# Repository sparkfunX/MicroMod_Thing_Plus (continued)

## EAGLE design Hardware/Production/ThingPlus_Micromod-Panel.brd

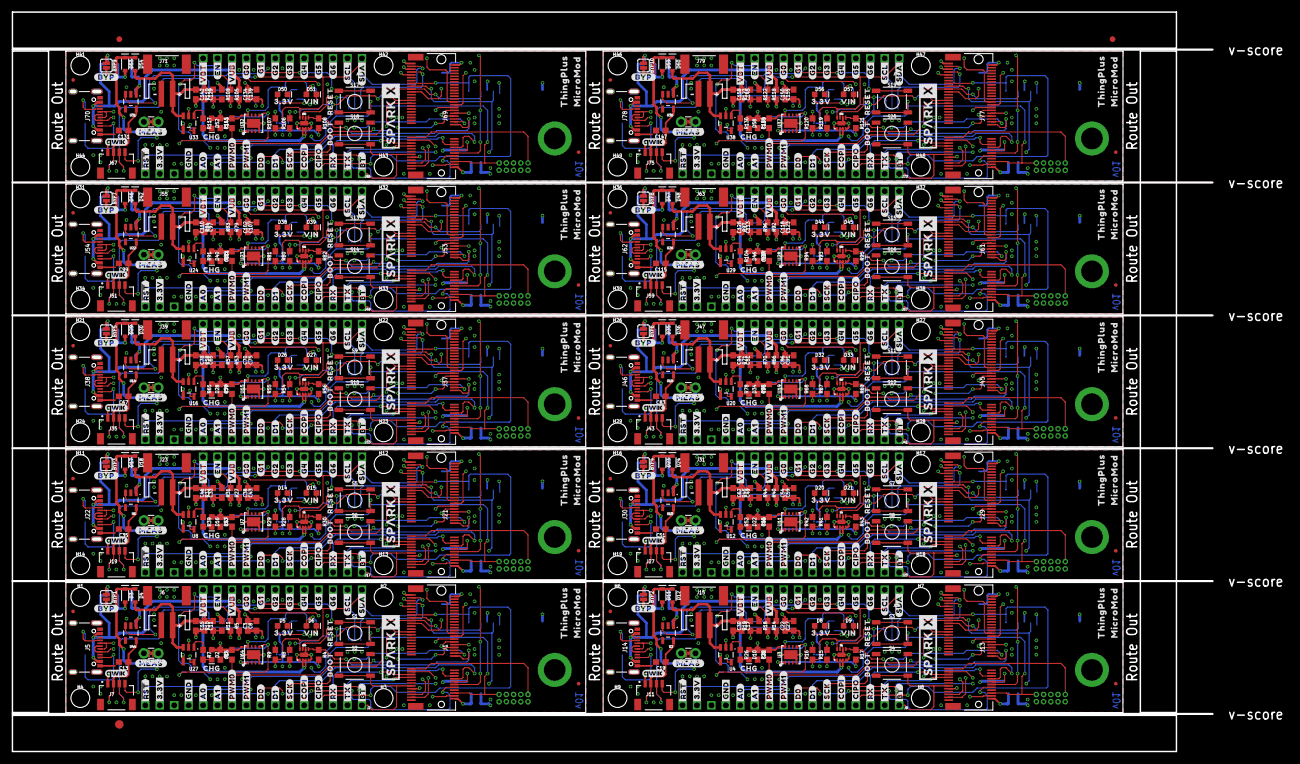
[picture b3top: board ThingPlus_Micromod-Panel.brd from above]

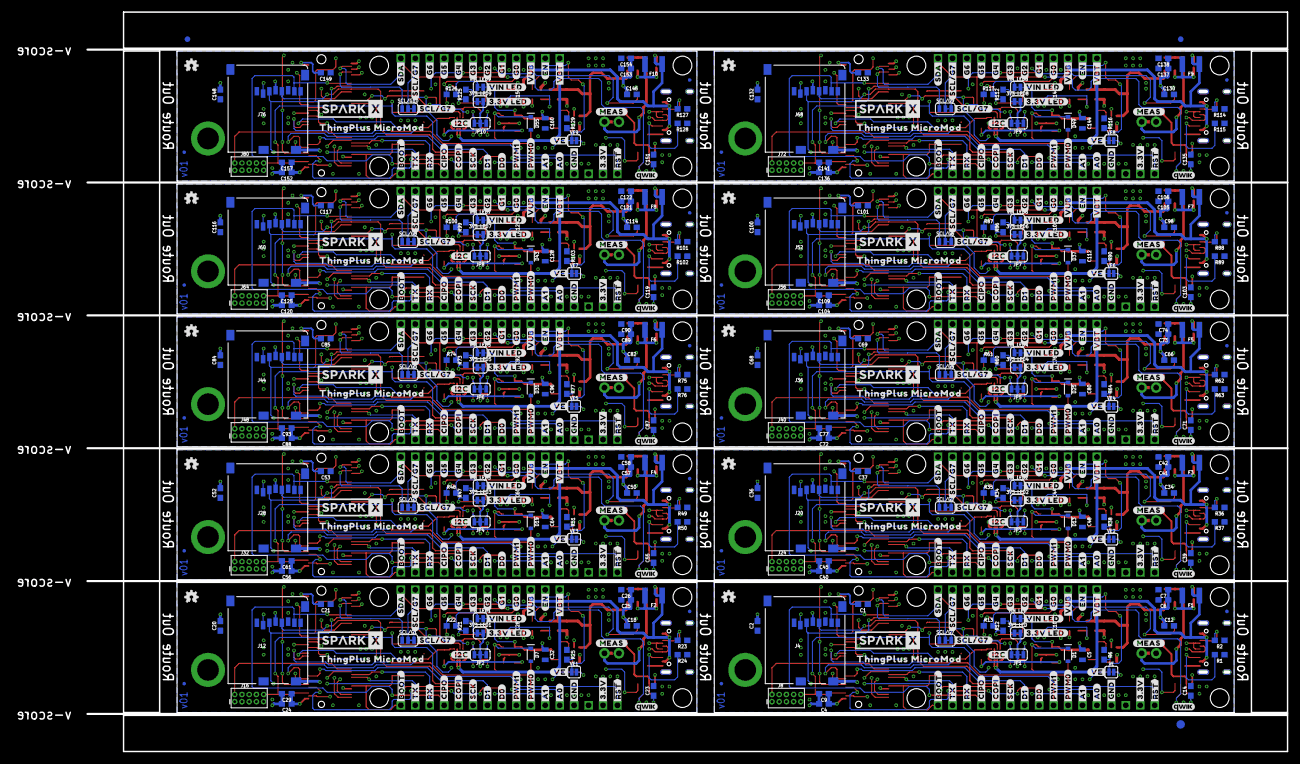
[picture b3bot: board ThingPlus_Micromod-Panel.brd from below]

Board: 4 copper layers, 211.1 x 130.0 mm, 1446 parts (623 on the bottom side), 530 nets.

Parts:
3V3_LED, 3V3_LED1, 3V3_LED2, 3V3_LED3, 3V3_LED4, 3V3_LED5, 3V3_LED6, 3V3_LED7, 3V3_LED8, 3V3_LED9: SMT-JUMPER_2_NC_TRACE_SILK
BYP1, BYP2, BYP3, BYP4, BYP5, BYP6, BYP7, BYP8, BYP9, BYP10: JUMPER-SMT_2_NO_SILK; SMT-JUMPER_2_NO_SILK
C1, C3, C4, C7, C10, C11, C14, C17, C21, C22, C23, C24, C26, C28, C33, C37, C38, C39, C40, C42, C44, C49, C53, C54, C55, C56, C58, C60, C65, C69, C70, C71, C72, C74, C76, C81, C85, C86, C87, C88, C90, C92, C97, C101, C102, C103, C104, C106, C108, C113, C117, C118, C119, C120, C122, C124, C129, C133, C134, C135, C136, C138, C140, C145, C149, C150, C151, C152, C154, C156: 0.1uF; 0603
C2, C8, C12, C13, C18, C19, C20, C27, C34, C35, C36, C43, C50, C51, C52, C59, C66, C67, C68, C75, C82, C83, C84, C91, C98, C99, C100, C107, C114, C115, C116, C123, C130, C131, C132, C139, C146, C147, C148, C155: 1.0uF; 0603
C5, C32, C48, C64, C80, C96, C112, C128, C144, C160: 10uF; 0805
C6, C9, C25, C29, C41, C45, C57, C61, C73, C77, C89, C93, C105, C109, C121, C125, C137, C141, C153, C157: 0.22uF; 0603
C15, C16, C30, C31, C46, C47, C62, C63, C78, C79, C94, C95, C110, C111, C126, C127, C142, C143, C158, C159: 4.7uF; 0603
CURR_MEAS, CURR_MEAS1, CURR_MEAS2, CURR_MEAS3, CURR_MEAS4, CURR_MEAS5, CURR_MEAS6, CURR_MEAS7, CURR_MEAS8, CURR_MEAS9: COMBO-JUMPER_2_NC_TRACE
D1, D7, D13, D19, D25, D31, D37, D43, D49, D55: 3.3V; SOD-323
D2, D6, D9, D10, D15, D16, D21, D22, D27, D28, D33, D34, D39, D40, D45, D46, D51, D52, D57, D58: Yellow; LED-0603
D3, D4, D11, D12, D17, D18, D23, D24, D29, D30, D35, D36, D41, D42, D47, D48, D53, D54, D59, D60: 3A/10V/280mV; SOD-323
D5, D8, D14, D20, D26, D32, D38, D44, D50, D56: RED; LED-0603
E$1, E$2, E$3, E$4: FIDUCIAL-1X2
E$5, E$6: FIDUCIAL-1.5X3
F1, F2, F3, F4, F5, F6, F7, F8, F9, F10: 6V/2A; 1210
FD1, FD2, FD3, FD4, FD5, FD6, FD7, FD8, FD9, FD10, FD11, FD12, FD13, FD14, FD15, FD16, FD17, FD18, FD19, FD20, FD21, FD22, FD23, FD24, FD25, FD26, FD27, FD28, FD29, FD30, FD31, FD32, FD33, FD34, FD35, FD36, FD37, FD38, FD39, FD40: FIDUCIALUFIDUCIAL; FIDUCIAL-MICRO
FRAME1, FRAME2, FRAME3, FRAME4, FRAME5, FRAME6, FRAME7, FRAME8, FRAME9, FRAME10: FRAME-LEDGER; CREATIVE_COMMONS
H1, H2, H3, H4, H6, H7, H8, H9, H11, H12, H13, H14, H16, H17, H18, H19, H21, H22, H23, H24, H26, H27, H28, H29, H31, H32, H33, H34, H36, H37, H38, H39, H41, H42, H43, H44, H46, H47, H48, H49: STAND-OFF
H5, H10, H15, H20, H25, H30, H35, H40, H45, H50: STAND-OFF-REFLOW2.5MM_TALL; STAND-OFF-REFLOW-M2.5
J1, J13, J21, J29, J37, J45, J53, J61, J69, J77: MICROMOD-2222-C; M.2-CONNECTOR-E
J2, J9, J17, J25, J33, J41, J49, J57, J65, J73: 1X16_SM_SQ_NOSILK
J3, J10, J18, J26, J34, J42, J50, J58, J66, J74: 1X12_SM_SQ_NOSILK
J4, J12, J20, J28, J36, J44, J52, J60, J68, J76: MICRO-SD-SDIOPUSH-PUSH; MICRO-SD-SOCKET
J5, J14, J22, J30, J38, J46, J54, J62, J70, J78: USB-C-16P_4LAYER-PADS
J6, J15, J23, J31, J39, J47, J55, J63, J71, J79: JST-2-SMD
J7, J11, J19, J27, J35, J43, J51, J59, J67, J75: QWIIC_RIGHT_ANGLE; JST04_1MM_RA
J8, J16, J24, J32, J40, J48, J56, J64, J72, J80: JTAG; 2X5-PTH-1.27MM
JP1, JP2, JP3, JP4, JP5, JP6, JP7, JP8, JP9, JP10: JUMPER-SMT_3_2-NC_TRACE_SILK; SMT-JUMPER_3_2-NC_TRACE_SILK
LOGO1, LOGO4, LOGO7, LOGO10, LOGO13, LOGO16, LOGO19, LOGO22, LOGO25, LOGO28: OSHW-LOGOMINI; OSHW-LOGO-MINI
LOGO2, LOGO3, LOGO5, LOGO6, LOGO8, LOGO9, LOGO11, LOGO12, LOGO14, LOGO15, LOGO17, LOGO18, LOGO20, LOGO21, LOGO23, LOGO24, LOGO26, LOGO27, LOGO29, LOGO30: QWIIC_LOGO_4MM; QWIIC_4MM
R1, R2, R23, R24, R36, R37, R49, R50, R62, R63, R75, R76, R88, R89, R101, R102, R114, R115, R127, R128: 5.1k; 0603
R3, R5, R14, R20, R27, R33, R40, R46, R53, R59, R66, R72, R79, R85, R92, R98, R105, R111, R118, R124: 100k; 0603
R4, R11, R17, R18, R30, R31, R43, R44, R56, R57, R69, R70, R82, R83, R95, R96, R108, R109, R121, R122: 10k; 0603
R6, R8, R9, R15, R16, R25, R28, R29, R38, R41, R42, R51, R54, R55, R64, R67, R68, R77, R80, R81, R90, R93, R94, R103, R106, R107, R116, R119, R120, R129: 2.2k; 0603
R7, R12, R21, R26, R34, R39, R47, R52, R60, R65, R73, R78, R86, R91, R99, R104, R112, R117, R125, R130: 1k; 0603
R10, R19, R32, R45, R58, R71, R84, R97, R110, R123: 20k; 0603
R13, R22, R35, R48, R61, R74, R87, R100, R113, R126: 4.7k; 0603
S1, S3, S5, S7, S9, S11, S13, S15, S17, S19: Reset; TACTILE_SWITCH_SMD_5.2MM
S2, S4, S6, S8, S10, S12, S14, S16, S18, S20: BOOT; TACTILE_SWITCH_SMD_5.2MM
SCL/G1, SCL/G2, SCL/G3, SCL/G4, SCL/G5, SCL/G6, SCL/G7, SCL/G8, SCL/G9, SCL/G10: JUMPER-SMT_3_1-NC_TRACE_SILK; SMT-JUMPER_3_1-NC_TRACE_SILK
U1, U5, U9, U13, U17, U21, U25, U30, U34, U35: MAX17048; DFN-8
U2, U6, U10, U14, U18, U22, U26, U31, U36, U44: 3.3V; SOT23-5
U3, U7, U11, U15, U19, U23, U28, U32, U37, U64: AP7361C-33; UDFN-8
U4, U8, U12, U16, U20, U24, U27, U29, U33, U38: MCP73831; SOT23-5
U$1, U$2, U$75, U$76, U$149, U$150, U$223, U$224, U$297, U$298, U$371, U$372, U$445, U$446, U$519, U$520, U$593, U$594, U$667, U$668: SPARKX-LOGO5; SPARKX-LARGE
U$3, U$77, U$151, U$225, U$299, U$373, U$447, U$521, U$595, U$669: ##BT##11
U$4, U$42, U$78, U$114, U$152, U$188, U$226, U$262, U$300, U$336, U$374, U$410, U$448, U$484, U$522, U$558, U$596, U$632, U$670, U$706: #TX#9
U$5, U$43, U$79, U$115, U$153, U$189, U$227, U$263, U$301, U$337, U$375, U$411, U$449, U$485, U$523, U$559, U$597, U$633, U$671, U$707: #RX#8
U$6, U$44, U$80, U$116, U$154, U$190, U$228, U$264, U$302, U$338, U$376, U$412, U$450, U$486, U$524, U$560, U$598, U$634, U$672, U$708: #CIPO#7
U$7, U$45, U$81, U$117, U$155, U$191, U$229, U$265, U$303, U$339, U$377, U$413, U$451, U$487, U$525, U$561, U$599, U$635, U$673, U$709: #COPI#6
U$8, U$46, U$82, U$118, U$156, U$192, U$230, U$266, U$304, U$340, U$378, U$414, U$452, U$488, U$526, U$562, U$600, U$636, U$674, U$710: #SCK#5
U$9, U$47, U$83, U$119, U$157, U$193, U$231, U$267, U$305, U$341, U$379, U$415, U$453, U$489, U$527, U$563, U$601, U$637, U$675, U$711: #D1#5
U$10, U$48, U$84, U$120, U$158, U$194, U$232, U$268, U$306, U$342, U$380, U$416, U$454, U$490, U$528, U$564, U$602, U$638, U$676, U$712: #D0#5
U$11, U$49, U$85, U$121, U$159, U$195, U$233, U$269, U$307, U$343, U$381, U$417, U$455, U$491, U$529, U$565, U$603, U$639, U$677, U$713: #PWM0#5
U$12, U$50, U$86, U$122, U$160, U$196, U$234, U$270, U$308, U$344, U$382, U$418, U$456, U$492, U$530, U$566, U$604, U$640, U$678, U$714: #PWM1#5
U$13, U$51, U$87, U$123, U$161, U$197, U$235, U$271, U$309, U$345, U$383, U$419, U$457, U$493, U$531, U$567, U$605, U$641, U$679, U$715: #A1#5
U$14, U$52, U$88, U$124, U$162, U$198, U$236, U$272, U$310, U$346, U$384, U$420, U$458, U$494, U$532, U$568, U$606, U$642, U$680, U$716: #A0#5
U$15, U$53, U$89, U$125, U$163, U$199, U$237, U$273, U$311, U$347, U$385, U$421, U$459, U$495, U$533, U$569, U$607, U$643, U$681, U$717: #GND#4
U$16, U$54, U$90, U$126, U$164, U$200, U$238, U$274, U$312, U$348, U$386, U$422, U$460, U$496, U$534, U$570, U$608, U$644, U$682, U$718: #3#3V#1
U$17, U$55, U$91, U$127, U$165, U$201, U$239, U$275, U$313, U$349, U$387, U$423, U$461, U$497, U$535, U$571, U$609, U$645, U$683, U$719: ##RST##0
U$18, U$66, U$92, U$140, U$166, U$214, U$240, U$288, U$314, U$362, U$388, U$436, U$462, U$510, U$536, U$584, U$610, U$658, U$684, U$732: #MEAS#25
U$19, U$93, U$167, U$241, U$315, U$389, U$463, U$537, U$611, U$685: CHG20
U$20, U$94, U$168, U$242, U$316, U$390, U$464, U$538, U$612, U$686: RESET19
U$21, U$95, U$169, U$243, U$317, U$391, U$465, U$539, U$613, U$687: BOOT18
U$22, U$57, U$96, U$129, U$170, U$203, U$244, U$277, U$318, U$351, U$392, U$425, U$466, U$499, U$540, U$573, U$614, U$647, U$688, U$721: #VBT#16
U$23, U$58, U$97, U$130, U$171, U$204, U$245, U$278, U$319, U$352, U$393, U$426, U$467, U$500, U$541, U$574, U$615, U$648, U$689, U$722: #EN#15
U$24, U$59, U$98, U$131, U$172, U$205, U$246, U$279, U$320, U$353, U$394, U$427, U$468, U$501, U$542, U$575, U$616, U$649, U$690, U$723: #G0#14
U$25, U$60, U$99, U$132, U$173, U$206, U$247, U$280, U$321, U$354, U$395, U$428, U$469, U$502, U$543, U$576, U$617, U$650, U$691, U$724: #G1#14
U$26, U$61, U$100, U$133, U$174, U$207, U$248, U$281, U$322, U$355, U$396, U$429, U$470, U$503, U$544, U$577, U$618, U$651, U$692, U$725: #G2#14
U$27, U$62, U$101, U$134, U$175, U$208, U$249, U$282, U$323, U$356, U$397, U$430, U$471, U$504, U$545, U$578, U$619, U$652, U$693, U$726: #G3#14
U$28, U$63, U$102, U$135, U$176, U$209, U$250, U$283, U$324, U$357, U$398, U$431, U$472, U$505, U$546, U$579, U$620, U$653, U$694, U$727: #G4#14
U$29, U$64, U$103, U$136, U$177, U$210, U$251, U$284, U$325, U$358, U$399, U$432, U$473, U$506, U$547, U$580, U$621, U$654, U$695, U$728: #G5#14
U$30, U$65, U$104, U$137, U$178, U$211, U$252, U$285, U$326, U$359, U$400, U$433, U$474, U$507, U$548, U$581, U$622, U$655, U$696, U$729: #G6#14
U$31, U$105, U$179, U$253, U$327, U$401, U$475, U$549, U$623, U$697: #SCL#13
U$32, U$67, U$106, U$138, U$180, U$212, U$254, U$286, U$328, U$360, U$402, U$434, U$476, U$508, U$550, U$582, U$624, U$656, U$698, U$730: #SDA#12
U$33, U$107, U$181, U$255, U$329, U$403, U$477, U$551, U$625, U$699: 3#3V22
U$34, U$108, U$182, U$256, U$330, U$404, U$478, U$552, U$626, U$700: VIN21
U$35, U$68, U$109, U$139, U$183, U$213, U$257, U$287, U$331, U$361, U$405, U$435, U$479, U$509, U$553, U$583, U$627, U$657, U$701, U$731: #VUB#15
U$36, U$110, U$184, U$258, U$332, U$406, U$480, U$554, U$628, U$702: THINGPLUS29
U$37, U$111, U$185, U$259, U$333, U$407, U$481, U$555, U$629, U$703: MICROMOD30
U$38, U$112, U$186, U$260, U$334, U$408, U$482, U$556, U$630, U$704: #31
U$39, U$148, U$222, U$296, U$370, U$444, U$518, U$592, U$666, U$740: #33
U$40, U$113, U$187, U$261, U$335, U$409, U$483, U$557, U$631, U$705: #BYP#27
U$41, U$147, U$221, U$295, U$369, U$443, U$517, U$591, U$665, U$739: #VE#16
U$56, U$128, U$202, U$276, U$350, U$424, U$498, U$572, U$646, U$720: ##BOOT##10
U$69, U$141, U$215, U$289, U$363, U$437, U$511, U$585, U$659, U$733: #3#3V_LED#25
U$70, U$143, U$217, U$291, U$365, U$439, U$513, U$587, U$661, U$735: #VIN_LED#25
U$71, U$145, U$219, U$293, U$367, U$441, U$515, U$589, U$663, U$737: #SCL#G7#14
U$72, U$142, U$216, U$290, U$364, U$438, U$512, U$586, U$660, U$734: #I2C#27
U$73, U$146, U$220, U$294, U$368, U$442, U$516, U$590, U$664, U$738: THINGPLUS_MICROMOD29
U$74, U$144, U$218, U$292, U$366, U$440, U$514, U$588, U$662, U$736: #SCL#G7#27
VE, VE1, VE2, VE3, VE4, VE5, VE6, VE7, VE8, VE9: SMT-JUMPER_2_NO_SILK
VIN_LED, VIN_LED1, VIN_LED2, VIN_LED3, VIN_LED4, VIN_LED5, VIN_LED6, VIN_LED7, VIN_LED8, VIN_LED9: SMT-JUMPER_2_NC_TRACE_SILK

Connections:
3.3V: 3V3_LED.2, C1.2, C2.2, C4.1, C8.1, C9.1, C10.1, J1.2, J1.74, J2.15, J4.VCC, J8.1, JP1.2, R4.2, R5.2, U64.1
3.3V1: 3V3_LED1.2, C20.2, C21.2, C24.1, C27.1, C28.1, C29.1, J9.15, J12.VCC, J13.2, J13.74, J16.1, JP2.2, R14.2, R17.2, U3.1
3.3V2: 3V3_LED2.2, C36.2, C37.2, C40.1, C43.1, C44.1, C45.1, J17.15, J20.VCC, J21.2, J21.74, J24.1, JP3.2, R27.2, R30.2, U7.1
3.3V3: 3V3_LED3.2, C52.2, C53.2, C56.1, C59.1, C60.1, C61.1, J25.15, J28.VCC, J29.2, J29.74, J32.1, JP4.2, R40.2, R43.2, U11.1
3.3V4: 3V3_LED4.2, C68.2, C69.2, C72.1, C75.1, C76.1, C77.1, J33.15, J36.VCC, J37.2, J37.74, J40.1, JP5.2, R53.2, R56.2, U15.1
3.3V5: 3V3_LED5.2, C84.2, C85.2, C88.1, C91.1, C92.1, C93.1, J41.15, J44.VCC, J45.2, J45.74, J48.1, JP6.2, R66.2, R69.2, U19.1
3.3V6: 3V3_LED6.2, C100.2, C101.2, C104.1, C107.1, C108.1, C109.1, J49.15, J52.VCC, J53.2, J53.74, J56.1, JP7.2, R79.2, R82.2, U23.1
3.3V7: 3V3_LED7.2, C116.2, C117.2, C120.1, C123.1, C124.1, C125.1, J57.15, J60.VCC, J61.2, J61.74, J64.1, JP8.2, R92.2, R95.2, U28.1
3.3V8: 3V3_LED8.2, C132.2, C133.2, C136.1, C139.1, C140.1, C141.1, J65.15, J68.VCC, J69.2, J69.74, J72.1, JP9.2, R105.2, R108.2, U32.1
3.3V9: 3V3_LED9.2, C148.2, C149.2, C152.1, C155.1, C156.1, C157.1, J73.15, J76.VCC, J77.2, J77.74, J80.1, JP10.2, R118.2, R121.2, U37.1
3.3V_EN_VE: D1.C, R3.1, U64.5, VE.2
3.3V_EN_VE1: D7.C, R20.1, U3.5, VE1.2
3.3V_EN_VE2: D13.C, R33.1, U7.5, VE2.2
3.3V_EN_VE3: D19.C, R46.1, U11.5, VE3.2
3.3V_EN_VE4: D25.C, R59.1, U15.5, VE4.2
3.3V_EN_VE5: D31.C, R72.1, U19.5, VE5.2
3.3V_EN_VE6: D37.C, R85.1, U23.5, VE6.2
3.3V_EN_VE7: D43.C, R98.1, U28.5, VE7.2
3.3V_EN_VE8: D49.C, R111.1, U32.5, VE8.2
3.3V_EN_VE9: D55.C, R124.1, U37.5, VE9.2
!BOOT!: J1.11, J2.1, S2.3, S2.4
!BOOT!1: J9.1, J13.11, S4.3, S4.4
!BOOT!2: J17.1, J21.11, S6.3, S6.4
!BOOT!3: J25.1, J29.11, S8.3, S8.4
!BOOT!4: J33.1, J37.11, S10.3, S10.4
!BOOT!5: J41.1, J45.11, S12.3, S12.4
!BOOT!6: J49.1, J53.11, S14.3, S14.4
!BOOT!7: J57.1, J61.11, S16.3, S16.4
!BOOT!8: J65.1, J69.11, S18.3, S18.4
!BOOT!9: J73.1, J77.11, S20.3, S20.4
!I2C_INT!: J1.16, R4.1, U34.5
!I2C_INT!1: J13.16, R17.1, U1.5
!I2C_INT!2: J21.16, R30.1, U5.5
!I2C_INT!3: J29.16, R43.1, U9.5
!I2C_INT!4: J37.16, R56.1, U13.5
!I2C_INT!5: J45.16, R69.1, U17.5
!I2C_INT!6: J53.16, R82.1, U21.5
!I2C_INT!7: J61.16, R95.1, U25.5
!I2C_INT!8: J69.16, R108.1, U30.5
!I2C_INT!9: J77.16, R121.1, U35.5
!RST!: J1.6, J2.16, J8.10, S1.3, S1.4
!RST!1: J9.16, J13.6, J16.10, S3.3, S3.4
!RST!2: J17.16, J21.6, J24.10, S5.3, S5.4
!RST!3: J25.16, J29.6, J32.10, S7.3, S7.4
!RST!4: J33.16, J37.6, J40.10, S9.3, S9.4
!RST!5: J41.16, J45.6, J48.10, S11.3, S11.4
!RST!6: J49.16, J53.6, J56.10, S13.3, S13.4
!RST!7: J57.16, J61.6, J64.10, S15.3, S15.4
!RST!8: J65.16, J69.6, J72.10, S17.3, S17.4
!RST!9: J73.16, J77.6, J80.10, S19.3, S19.4
!SD_CS!: J1.55, J4.CS/DAT3
!SD_CS!1: J12.CS/DAT3, J13.55
!SD_CS!2: J20.CS/DAT3, J21.55
!SD_CS!3: J28.CS/DAT3, J29.55
!SD_CS!4: J36.CS/DAT3, J37.55
!SD_CS!5: J44.CS/DAT3, J45.55
!SD_CS!6: J52.CS/DAT3, J53.55
!SD_CS!7: J60.CS/DAT3, J61.55
!SD_CS!8: J68.CS/DAT3, J69.55
!SD_CS!9: J76.CS/DAT3, J77.55
A0: J1.34, J2.12
A1: J1.38, J2.11
A2: J9.12, J13.34
A3: J9.11, J13.38
A4: J17.12, J21.34
A5: J17.11, J21.38
A6: J25.12, J29.34
A7: J25.11, J29.38
A8: J33.12, J37.34
A9: J33.11, J37.38
A10: J41.12, J45.34
A11: J41.11, J45.38
A12: J49.12, J53.34
A13: J49.11, J53.38
A14: J57.12, J61.34
A15: J57.11, J61.38
A16: J65.12, J69.34
A17: J65.11, J69.38
A18: J73.12, J77.34
A19: J73.11, J77.38
BATT_VIN/1: J13.49, R18.2, R19.1
BATT_VIN/2: J21.49, R31.2, R32.1
BATT_VIN/3: J1.49, R10.1, R11.2
BATT_VIN/4: J29.49, R44.2, R45.1
BATT_VIN/5: J37.49, R57.2, R58.1
BATT_VIN/6: J45.49, R70.2, R71.1
BATT_VIN/7: J53.49, R83.2, R84.1
BATT_VIN/8: J61.49, R96.2, R97.1
BATT_VIN/9: J69.49, R109.2, R110.1
BATT_VIN/10: J77.49, R122.2, R123.1
CHG_LED: R7.1, U27.1
CHG_LED1: R26.1, U4.1
CHG_LED2: R39.1, U8.1
CHG_LED3: R52.1, U12.1
CHG_LED4: R65.1, U16.1
CHG_LED5: R78.1, U20.1
CHG_LED6: R91.1, U24.1
CHG_LED7: R104.1, U29.1
CHG_LED8: R117.1, U33.1
CHG_LED9: R130.1, U38.1
D0: J1.10, J2.8
D1: J1.18, J2.7
D2: J9.8, J13.10
D3: J9.7, J13.18
D4: J17.8, J21.10
D5: J17.7, J21.18
D6: J25.8, J29.10
D7: J25.7, J29.18
D8: J33.8, J37.10
D9: J33.7, J37.18
D10: J41.8, J45.10
D11: J41.7, J45.18
D12: J49.8, J53.10
D13: J49.7, J53.18
D14: J57.8, J61.10
D15: J57.7, J61.18
D16: J65.8, J69.10
D17: J65.7, J69.18
D18: J73.8, J77.10
D19: J73.7, J77.18
EN: J1.4, J3.11, VE.1
EN1: J10.11, J13.4, VE1.1
EN2: J18.11, J21.4, VE2.1
EN3: J26.11, J29.4, VE3.1
EN4: J34.11, J37.4, VE4.1
EN5: J42.11, J45.4, VE5.1
EN6: J50.11, J53.4, VE6.1
EN7: J58.11, J61.4, VE7.1
EN8: J66.11, J69.4, VE8.1
EN9: J74.11, J77.4, VE9.1
G0: J1.40, J3.9
G1: J1.42, J3.8
G2: J1.44, J3.7
G3: J1.46, J3.6
G4: J1.48, J3.5
G5: J1.73, J3.4
G6: J1.71, J3.3
G7: J1.69, SCL/G7.1
G8: J10.9, J13.40
G9: J10.8, J13.42
G10: J10.6, J13.46
G11: J10.3, J13.71
G12: J10.4, J13.73
G13: J10.5, J13.48
G14: J10.7, J13.44
G15: J13.69, SCL/G1.1
G16: J18.9, J21.40
G17: J18.8, J21.42
G18: J18.6, J21.46
G19: J18.3, J21.71
G20: J18.4, J21.73
G21: J18.5, J21.48
G22: J18.7, J21.44
G23: J21.69, SCL/G2.1
G24: J26.9, J29.40
G25: J26.8, J29.42
G26: J26.6, J29.46
G27: J26.3, J29.71
G28: J26.4, J29.73
G29: J26.5, J29.48
G30: J26.7, J29.44
G31: J29.69, SCL/G3.1
G32: J34.9, J37.40
G33: J34.8, J37.42
G34: J34.6, J37.46
G35: J34.3, J37.71
G36: J34.4, J37.73
G37: J34.5, J37.48
G38: J34.7, J37.44
G39: J37.69, SCL/G4.1
G40: J42.9, J45.40
G41: J42.8, J45.42
G42: J42.6, J45.46
G43: J42.3, J45.71
G44: J42.4, J45.73
G45: J42.5, J45.48
G46: J42.7, J45.44
G47: J45.69, SCL/G5.1
G48: J50.9, J53.40
G49: J50.8, J53.42
G50: J50.6, J53.46
G51: J50.3, J53.71
G52: J50.4, J53.73
G53: J50.5, J53.48
G54: J50.7, J53.44
G55: J53.69, SCL/G6.1
G56: J58.9, J61.40
G57: J58.8, J61.42
G58: J58.6, J61.46
G59: J58.3, J61.71
G60: J58.4, J61.73
G61: J58.5, J61.48
G62: J58.7, J61.44
G63: J61.69, SCL/G8.1
G64: J66.9, J69.40
G65: J66.8, J69.42
G66: J66.6, J69.46
G67: J66.3, J69.71
G68: J66.4, J69.73
G69: J66.5, J69.48
G70: J66.7, J69.44
G71: J69.69, SCL/G9.1
G72: J74.9, J77.40
G73: J74.8, J77.42
G74: J74.6, J77.46
G75: J74.3, J77.71
G76: J74.4, J77.73
G77: J74.5, J77.48
G78: J74.7, J77.44
G79: J77.69, SCL/G10.1
GND: C1.1, C2.1, C3.2, C4.2, C5.2, C6.2, C7.2, C8.2, C9.2, C10.2, C11.2, C12.2, C13.2, C14.2, C15.2, C16.2, D1.A, D5.C, D6.C, H5.1, J1.1, J1.7, J1.33, J1.36, J1.39, J1.45, J1.75, J2.13, J4.CD1, J4.GND, J4.GND1, J4.GND3, J5.GND, J5.GND2, J5.SHLD1, J5.SHLD2, J5.SHLD3, J5.SHLD4, J6.1, J7.1, J8.3, J8.5, J8.9, R1.1, R2.1, R6.1, R11.1, S1.1, S1.2, S2.1, S2.2, U27.2, U34.1, U34.4, U34.6, U34.9, U44.2, U64.4, U64.EP
GND1: C17.2, C18.2, C19.2, C20.1, C21.1, C22.2, C23.2, C24.2, C25.2, C26.2, C27.2, C28.2, C29.2, C30.2, C31.2, C32.2, D7.A, D8.C, D9.C, H10.1, J9.13, J11.1, J12.CD1, J12.GND, J12.GND1, J12.GND3, J13.1, J13.7, J13.33, J13.36, J13.39, J13.45, J13.75, J14.GND, J14.GND2, J14.SHLD1, J14.SHLD2, J14.SHLD3, J14.SHLD4, J15.1, J16.3, J16.5, J16.9, R18.1, R23.1, R24.1, R25.1, S3.1, S3.2, S4.1, S4.2, U1.1, U1.4, U1.6, U1.9, U2.2, U3.4, U3.EP, U4.2
GND2: C33.2, C34.2, C35.2, C36.1, C37.1, C38.2, C39.2, C40.2, C41.2, C42.2, C43.2, C44.2, C45.2, C46.2, C47.2, C48.2, D13.A, D14.C, D15.C, H15.1, J17.13, J19.1, J20.CD1, J20.GND, J20.GND1, J20.GND3, J21.1, J21.7, J21.33, J21.36, J21.39, J21.45, J21.75, J22.GND, J22.GND2, J22.SHLD1, J22.SHLD2, J22.SHLD3, J22.SHLD4, J23.1, J24.3, J24.5, J24.9, R31.1, R36.1, R37.1, R38.1, S5.1, S5.2, S6.1, S6.2, U5.1, U5.4, U5.6, U5.9, U6.2, U7.4, U7.EP, U8.2
GND3: C49.2, C50.2, C51.2, C52.1, C53.1, C54.2, C55.2, C56.2, C57.2, C58.2, C59.2, C60.2, C61.2, C62.2, C63.2, C64.2, D19.A, D20.C, D21.C, H20.1, J25.13, J27.1, J28.CD1, J28.GND, J28.GND1, J28.GND3, J29.1, J29.7, J29.33, J29.36, J29.39, J29.45, J29.75, J30.GND, J30.GND2, J30.SHLD1, J30.SHLD2, J30.SHLD3, J30.SHLD4, J31.1, J32.3, J32.5, J32.9, R44.1, R49.1, R50.1, R51.1, S7.1, S7.2, S8.1, S8.2, U9.1, U9.4, U9.6, U9.9, U10.2, U11.4, U11.EP, U12.2
GND4: C65.2, C66.2, C67.2, C68.1, C69.1, C70.2, C71.2, C72.2, C73.2, C74.2, C75.2, C76.2, C77.2, C78.2, C79.2, C80.2, D25.A, D26.C, D27.C, H25.1, J33.13, J35.1, J36.CD1, J36.GND, J36.GND1, J36.GND3, J37.1, J37.7, J37.33, J37.36, J37.39, J37.45, J37.75, J38.GND, J38.GND2, J38.SHLD1, J38.SHLD2, J38.SHLD3, J38.SHLD4, J39.1, J40.3, J40.5, J40.9, R57.1, R62.1, R63.1, R64.1, S9.1, S9.2, S10.1, S10.2, U13.1, U13.4, U13.6, U13.9, U14.2, U15.4, U15.EP, U16.2
GND5: C81.2, C82.2, C83.2, C84.1, C85.1, C86.2, C87.2, C88.2, C89.2, C90.2, C91.2, C92.2, C93.2, C94.2, C95.2, C96.2, D31.A, D32.C, D33.C, H30.1, J41.13, J43.1, J44.CD1, J44.GND, J44.GND1, J44.GND3, J45.1, J45.7, J45.33, J45.36, J45.39, J45.45, J45.75, J46.GND, J46.GND2, J46.SHLD1, J46.SHLD2, J46.SHLD3, J46.SHLD4, J47.1, J48.3, J48.5, J48.9, R70.1, R75.1, R76.1, R77.1, S11.1, S11.2, S12.1, S12.2, U17.1, U17.4, U17.6, U17.9, U18.2, U19.4, U19.EP, U20.2
GND6: C97.2, C98.2, C99.2, C100.1, C101.1, C102.2, C103.2, C104.2, C105.2, C106.2, C107.2, C108.2, C109.2, C110.2, C111.2, C112.2, D37.A, D38.C, D39.C, H35.1, J49.13, J51.1, J52.CD1, J52.GND, J52.GND1, J52.GND3, J53.1, J53.7, J53.33, J53.36, J53.39, J53.45, J53.75, J54.GND, J54.GND2, J54.SHLD1, J54.SHLD2, J54.SHLD3, J54.SHLD4, J55.1, J56.3, J56.5, J56.9, R83.1, R88.1, R89.1, R90.1, S13.1, S13.2, S14.1, S14.2, U21.1, U21.4, U21.6, U21.9, U22.2, U23.4, U23.EP, U24.2
GND7: C113.2, C114.2, C115.2, C116.1, C117.1, C118.2, C119.2, C120.2, C121.2, C122.2, C123.2, C124.2, C125.2, C126.2, C127.2, C128.2, D43.A, D44.C, D45.C, H40.1, J57.13, J59.1, J60.CD1, J60.GND, J60.GND1, J60.GND3, J61.1, J61.7, J61.33, J61.36, J61.39, J61.45, J61.75, J62.GND, J62.GND2, J62.SHLD1, J62.SHLD2, J62.SHLD3, J62.SHLD4, J63.1, J64.3, J64.5, J64.9, R96.1, R101.1, R102.1, R103.1, S15.1, S15.2, S16.1, S16.2, U25.1, U25.4, U25.6, U25.9, U26.2, U28.4, U28.EP, U29.2
GND8: C129.2, C130.2, C131.2, C132.1, C133.1, C134.2, C135.2, C136.2, C137.2, C138.2, C139.2, C140.2, C141.2, C142.2, C143.2, C144.2, D49.A, D50.C, D51.C, H45.1, J65.13, J67.1, J68.CD1, J68.GND, J68.GND1, J68.GND3, J69.1, J69.7, J69.33, J69.36, J69.39, J69.45, J69.75, J70.GND, J70.GND2, J70.SHLD1, J70.SHLD2, J70.SHLD3, J70.SHLD4, J71.1, J72.3, J72.5, J72.9, R109.1, R114.1, R115.1, R116.1, S17.1, S17.2, S18.1, S18.2, U30.1, U30.4, U30.6, U30.9, U31.2, U32.4, U32.EP, U33.2
GND9: C145.2, C146.2, C147.2, C148.1, C149.1, C150.2, C151.2, C152.2, C153.2, C154.2, C155.2, C156.2, C157.2, C158.2, C159.2, C160.2, D55.A, D56.C, D57.C, H50.1, J73.13, J75.1, J76.CD1, J76.GND, J76.GND1, J76.GND3, J77.1, J77.7, J77.33, J77.36, J77.39, J77.45, J77.75, J78.GND, J78.GND2, J78.SHLD1, J78.SHLD2, J78.SHLD3, J78.SHLD4, J79.1, J80.3, J80.5, J80.9, R122.1, R127.1, R128.1, R129.1, S19.1, S19.2, S20.1, S20.2, U35.1, U35.4, U35.6, U35.9, U36.2, U37.4, U37.EP, U38.2
unnamed: 3V3_LED1.1, R21.2
unnamed: JP1.3, R8.2
unnamed: JP1.1, R9.2
unnamed: BYP1.2, D3.A, F1.2
unnamed: CURR_MEAS.1, CURR_MEAS.3, D3.C, D4.C
unnamed: 3V3_LED.1, R12.2
unnamed: D8.A, R21.1
unnamed: R6.2, U27.5
unnamed: D5.A, R12.1
unnamed: R13.2, VIN_LED.1
unnamed: D6.A, R13.1
unnamed: J5.A5, R2.2
unnamed: J5.B5, R1.2
unnamed: D2.C, R7.2
unnamed: R22.2, VIN_LED1.1
unnamed: D9.A, R22.1
unnamed: J14.A5, R23.2
unnamed: J14.B5, R24.2
unnamed: R25.2, U4.5
unnamed: D10.C, R26.2
unnamed: JP2.3, R15.2
unnamed: JP2.1, R16.2
unnamed: BYP2.2, D11.A, F2.2
unnamed: CURR_MEAS1.1, CURR_MEAS1.3, D11.C, D12.C
unnamed: 3V3_LED2.1, R34.2
unnamed: D14.A, R34.1
unnamed: R35.2, VIN_LED2.1
unnamed: D15.A, R35.1
unnamed: J22.A5, R36.2
unnamed: J22.B5, R37.2
unnamed: R38.2, U8.5
unnamed: D16.C, R39.2
unnamed: JP3.3, R28.2
unnamed: JP3.1, R29.2
unnamed: BYP3.2, D17.A, F3.2
unnamed: CURR_MEAS2.1, CURR_MEAS2.3, D17.C, D18.C
unnamed: 3V3_LED3.1, R47.2
unnamed: D20.A, R47.1
unnamed: R48.2, VIN_LED3.1
unnamed: D21.A, R48.1
unnamed: J30.A5, R49.2
unnamed: J30.B5, R50.2
unnamed: R51.2, U12.5
unnamed: D22.C, R52.2
unnamed: JP4.3, R41.2
unnamed: JP4.1, R42.2
unnamed: BYP4.2, D23.A, F4.2
unnamed: CURR_MEAS3.1, CURR_MEAS3.3, D23.C, D24.C
unnamed: 3V3_LED4.1, R60.2
unnamed: D26.A, R60.1
unnamed: R61.2, VIN_LED4.1
unnamed: D27.A, R61.1
unnamed: J38.A5, R62.2
unnamed: J38.B5, R63.2
unnamed: R64.2, U16.5
unnamed: D28.C, R65.2
unnamed: JP5.3, R54.2
unnamed: JP5.1, R55.2
unnamed: BYP5.2, D29.A, F5.2
unnamed: CURR_MEAS4.1, CURR_MEAS4.3, D29.C, D30.C
unnamed: 3V3_LED5.1, R73.2
unnamed: D32.A, R73.1
unnamed: R74.2, VIN_LED5.1
unnamed: D33.A, R74.1
unnamed: J46.A5, R75.2
unnamed: J46.B5, R76.2
unnamed: R77.2, U20.5
unnamed: D34.C, R78.2
unnamed: JP6.3, R67.2
unnamed: JP6.1, R68.2
unnamed: BYP6.2, D35.A, F6.2
unnamed: CURR_MEAS5.1, CURR_MEAS5.3, D35.C, D36.C
unnamed: 3V3_LED6.1, R86.2
unnamed: D38.A, R86.1
unnamed: R87.2, VIN_LED6.1
unnamed: D39.A, R87.1
unnamed: J54.A5, R88.2
unnamed: J54.B5, R89.2
unnamed: R90.2, U24.5
unnamed: D40.C, R91.2
unnamed: JP7.3, R80.2
unnamed: JP7.1, R81.2
unnamed: BYP7.2, D41.A, F7.2
unnamed: CURR_MEAS6.1, CURR_MEAS6.3, D41.C, D42.C
unnamed: 3V3_LED7.1, R99.2
unnamed: D44.A, R99.1
unnamed: R100.2, VIN_LED7.1
unnamed: D45.A, R100.1
unnamed: J62.A5, R101.2
unnamed: J62.B5, R102.2
unnamed: R103.2, U29.5
unnamed: D46.C, R104.2
unnamed: JP8.3, R93.2
unnamed: JP8.1, R94.2
unnamed: BYP8.2, D47.A, F8.2
unnamed: CURR_MEAS7.1, CURR_MEAS7.3, D47.C, D48.C
unnamed: 3V3_LED8.1, R112.2
unnamed: D50.A, R112.1
unnamed: R113.2, VIN_LED8.1
unnamed: D51.A, R113.1
unnamed: J70.A5, R114.2
unnamed: J70.B5, R115.2
unnamed: R116.2, U33.5
unnamed: D52.C, R117.2
unnamed: JP9.3, R106.2
unnamed: JP9.1, R107.2
unnamed: BYP9.2, D53.A, F9.2
unnamed: CURR_MEAS8.1, CURR_MEAS8.3, D53.C, D54.C
unnamed: 3V3_LED9.1, R125.2
unnamed: D56.A, R125.1
unnamed: R126.2, VIN_LED9.1
unnamed: D57.A, R126.1
unnamed: J78.A5, R127.2
unnamed: J78.B5, R128.2
unnamed: R129.2, U38.5
unnamed: D58.C, R130.2
unnamed: JP10.3, R119.2
unnamed: JP10.1, R120.2
unnamed: BYP10.2, D59.A, F10.2
unnamed: CURR_MEAS9.1, CURR_MEAS9.3, D59.C, D60.C
PWM0: J1.32, J2.10
PWM1: J1.47, J2.9
PWM2: J9.10, J13.32
PWM3: J9.9, J13.47
PWM4: J17.10, J21.32
PWM5: J17.9, J21.47
PWM6: J25.10, J29.32
PWM7: J25.9, J29.47
PWM8: J33.10, J37.32
PWM9: J33.9, J37.47
PWM10: J41.10, J45.32
PWM11: J41.9, J45.47
PWM12: J49.10, J53.32
PWM13: J49.9, J53.47
PWM14: J57.10, J61.32
PWM15: J57.9, J61.47
PWM16: J65.10, J69.32
PWM17: J65.9, J69.47
PWM18: J73.10, J77.32
PWM19: J73.9, J77.47
QWIIC_EN: J1.67, R5.1, U44.3
QWIIC_EN1: J13.67, R14.1, U2.3
QWIIC_EN2: J21.67, R27.1, U6.3
QWIIC_EN3: J29.67, R40.1, U10.3
QWIIC_EN4: J37.67, R53.1, U14.3
QWIIC_EN5: J45.67, R66.1, U18.3
QWIIC_EN6: J53.67, R79.1, U22.3
QWIIC_EN7: J61.67, R92.1, U26.3
QWIIC_EN8: J69.67, R105.1, U31.3
QWIIC_EN9: J77.67, R118.1, U36.3
QWIIC_PWR: C13.1, C14.1, J7.2, U44.5
QWIIC_PWR1: C19.1, C23.1, J11.2, U2.5
QWIIC_PWR2: C35.1, C39.1, J19.2, U6.5
QWIIC_PWR3: C51.1, C55.1, J27.2, U10.5
QWIIC_PWR4: C67.1, C71.1, J35.2, U14.5
QWIIC_PWR5: C83.1, C87.1, J43.2, U18.5
QWIIC_PWR6: C99.1, C103.1, J51.2, U22.5
QWIIC_PWR7: C115.1, C119.1, J59.2, U26.5
QWIIC_PWR8: C131.1, C135.1, J67.2, U31.5
QWIIC_PWR9: C147.1, C151.1, J75.2, U36.5
SCL: J1.14, J7.4, R8.1, SCL/G7.3, U34.7
SCL1: J11.4, J13.14, R15.1, SCL/G1.3, U1.7
SCL2: J19.4, J21.14, R28.1, SCL/G2.3, U5.7
SCL3: J27.4, J29.14, R41.1, SCL/G3.3, U9.7
SCL4: J35.4, J37.14, R54.1, SCL/G4.3, U13.7
SCL5: J43.4, J45.14, R67.1, SCL/G5.3, U17.7
SCL6: J51.4, J53.14, R80.1, SCL/G6.3, U21.7
SCL7: J59.4, J61.14, R93.1, SCL/G8.3, U25.7
SCL8: J67.4, J69.14, R106.1, SCL/G9.3, U30.7
SCL9: J75.4, J77.14, R119.1, SCL/G10.3, U35.7
SCL/G1: J10.2, SCL/G1.2
SCL/G2: J18.2, SCL/G2.2
SCL/G3: J26.2, SCL/G3.2
SCL/G4: J34.2, SCL/G4.2
SCL/G5: J42.2, SCL/G5.2
SCL/G6: J50.2, SCL/G6.2
SCL/G7: J3.2, SCL/G7.2
SCL/G8: J58.2, SCL/G8.2
SCL/G9: J66.2, SCL/G9.2
SCL/G10: J74.2, SCL/G10.2
SDA: J1.12, J3.1, J7.3, R9.1, U34.8
SDA1: J10.1, J11.3, J13.12, R16.1, U1.8
SDA2: J18.1, J19.3, J21.12, R29.1, U5.8
SDA3: J26.1, J27.3, J29.12, R42.1, U9.8
SDA4: J34.1, J35.3, J37.12, R55.1, U13.8
SDA5: J42.1, J43.3, J45.12, R68.1, U17.8
SDA6: J50.1, J51.3, J53.12, R81.1, U21.8
SDA7: J58.1, J59.3, J61.12, R94.1, U25.8
SDA8: J66.1, J67.3, J69.12, R107.1, U30.8
SDA9: J74.1, J75.3, J77.12, R120.1, U35.8
SPI_CIPO: J1.61, J2.4, J4.DO/DAT0
SPI_CIPO1: J9.4, J12.DO/DAT0, J13.61
SPI_CIPO2: J17.4, J20.DO/DAT0, J21.61
SPI_CIPO3: J25.4, J28.DO/DAT0, J29.61
SPI_CIPO4: J33.4, J36.DO/DAT0, J37.61
SPI_CIPO5: J41.4, J44.DO/DAT0, J45.61
SPI_CIPO6: J49.4, J52.DO/DAT0, J53.61
SPI_CIPO7: J57.4, J60.DO/DAT0, J61.61
SPI_CIPO8: J65.4, J68.DO/DAT0, J69.61
SPI_CIPO9: J73.4, J76.DO/DAT0, J77.61
SPI_COPI: J1.59, J2.5, J4.DI/CMD
SPI_COPI1: J9.5, J12.DI/CMD, J13.59
SPI_COPI2: J17.5, J20.DI/CMD, J21.59
SPI_COPI3: J25.5, J28.DI/CMD, J29.59
SPI_COPI4: J33.5, J36.DI/CMD, J37.59
SPI_COPI5: J41.5, J44.DI/CMD, J45.59
SPI_COPI6: J49.5, J52.DI/CMD, J53.59
SPI_COPI7: J57.5, J60.DI/CMD, J61.59
SPI_COPI8: J65.5, J68.DI/CMD, J69.59
SPI_COPI9: J73.5, J76.DI/CMD, J77.59
SPI_SCK: J1.57, J2.6, J4.SCLK
SPI_SCK1: J9.6, J12.SCLK, J13.57
SPI_SCK2: J17.6, J20.SCLK, J21.57
SPI_SCK3: J25.6, J28.SCLK, J29.57
SPI_SCK4: J33.6, J36.SCLK, J37.57
SPI_SCK5: J41.6, J44.SCLK, J45.57
SPI_SCK6: J49.6, J52.SCLK, J53.57
SPI_SCK7: J57.6, J60.SCLK, J61.57
SPI_SCK8: J65.6, J68.SCLK, J69.57
SPI_SCK9: J73.6, J76.SCLK, J77.57
SWDCK: J1.21, J8.4
SWDCK1: J13.21, J16.4
SWDCK2: J21.21, J24.4
SWDCK3: J29.21, J32.4
SWDCK4: J37.21, J40.4
SWDCK5: J45.21, J48.4
SWDCK6: J53.21, J56.4
SWDCK7: J61.21, J64.4
SWDCK8: J69.21, J72.4
SWDCK9: J77.21, J80.4
SWDIO: J1.23, J8.2
SWDIO1: J13.23, J16.2
SWDIO2: J21.23, J24.2
SWDIO3: J29.23, J32.2
SWDIO4: J37.23, J40.2
SWDIO5: J45.23, J48.2
SWDIO6: J53.23, J56.2
SWDIO7: J61.23, J64.2
SWDIO8: J69.23, J72.2
SWDIO9: J77.23, J80.2
UART_RX: J1.19, J2.3
UART_RX1: J9.3, J13.19
UART_RX2: J17.3, J21.19
UART_RX3: J25.3, J29.19
UART_RX4: J33.3, J37.19
UART_RX5: J41.3, J45.19
UART_RX6: J49.3, J53.19
UART_RX7: J57.3, J61.19
UART_RX8: J65.3, J69.19
UART_RX9: J73.3, J77.19
UART_TX: J1.17, J2.2
UART_TX1: J9.2, J13.17
UART_TX2: J17.2, J21.17
UART_TX3: J25.2, J29.17
UART_TX4: J33.2, J37.17
UART_TX5: J41.2, J45.17
UART_TX6: J49.2, J53.17
UART_TX7: J57.2, J61.17
UART_TX8: J65.2, J69.17
UART_TX9: J73.2, J77.17
USB_D+: J1.3, J5.A6, J5.B6
USB_D+1: J13.3, J14.A6, J14.B6
USB_D+2: J21.3, J22.A6, J22.B6
USB_D+3: J29.3, J30.A6, J30.B6
USB_D+4: J37.3, J38.A6, J38.B6
USB_D+5: J45.3, J46.A6, J46.B6
USB_D+6: J53.3, J54.A6, J54.B6
USB_D+7: J61.3, J62.A6, J62.B6
USB_D+8: J69.3, J70.A6, J70.B6
USB_D+9: J77.3, J78.A6, J78.B6
USB_D-: J1.5, J5.A7, J5.B7
USB_D-1: J13.5, J14.A7, J14.B7
USB_D-2: J21.5, J22.A7, J22.B7
USB_D-3: J29.5, J30.A7, J30.B7
USB_D-4: J37.5, J38.A7, J38.B7
USB_D-5: J45.5, J46.A7, J46.B7
USB_D-6: J53.5, J54.A7, J54.B7
USB_D-7: J61.5, J62.A7, J62.B7
USB_D-8: J69.5, J70.A7, J70.B7
USB_D-9: J77.5, J78.A7, J78.B7
VIN: C5.1, C6.1, C7.1, C12.1, C16.1, CURR_MEAS.2, CURR_MEAS.4, D2.A, R3.2, U27.4, U44.1, U64.8, VIN_LED.2
VIN1: C18.1, C25.1, C26.1, C31.1, C32.1, CURR_MEAS1.2, CURR_MEAS1.4, D10.A, R20.2, U2.1, U3.8, U4.4, VIN_LED1.2
VIN2: C34.1, C41.1, C42.1, C47.1, C48.1, CURR_MEAS2.2, CURR_MEAS2.4, D16.A, R33.2, U6.1, U7.8, U8.4, VIN_LED2.2
VIN3: C50.1, C57.1, C58.1, C63.1, C64.1, CURR_MEAS3.2, CURR_MEAS3.4, D22.A, R46.2, U10.1, U11.8, U12.4, VIN_LED3.2
VIN4: C66.1, C73.1, C74.1, C79.1, C80.1, CURR_MEAS4.2, CURR_MEAS4.4, D28.A, R59.2, U14.1, U15.8, U16.4, VIN_LED4.2
VIN5: C82.1, C89.1, C90.1, C95.1, C96.1, CURR_MEAS5.2, CURR_MEAS5.4, D34.A, R72.2, U18.1, U19.8, U20.4, VIN_LED5.2
VIN6: C98.1, C105.1, C106.1, C111.1, C112.1, CURR_MEAS6.2, CURR_MEAS6.4, D40.A, R85.2, U22.1, U23.8, U24.4, VIN_LED6.2
VIN7: C114.1, C121.1, C122.1, C127.1, C128.1, CURR_MEAS7.2, CURR_MEAS7.4, D46.A, R98.2, U26.1, U28.8, U29.4, VIN_LED7.2
VIN8: C130.1, C137.1, C138.1, C143.1, C144.1, CURR_MEAS8.2, CURR_MEAS8.4, D52.A, R111.2, U31.1, U32.8, U33.4, VIN_LED8.2
VIN9: C146.1, C153.1, C154.1, C159.1, C160.1, CURR_MEAS9.2, CURR_MEAS9.4, D58.A, R124.2, U36.1, U37.8, U38.4, VIN_LED9.2
V_BATT: C11.1, C15.1, D4.A, J3.12, J6.2, R10.2, U27.3, U34.2, U34.3
V_BATT1: C17.1, C30.1, D12.A, J10.12, J15.2, R19.2, U1.2, U1.3, U4.3
V_BATT2: C33.1, C46.1, D18.A, J18.12, J23.2, R32.2, U5.2, U5.3, U8.3
V_BATT3: C49.1, C62.1, D24.A, J26.12, J31.2, R45.2, U9.2, U9.3, U12.3
V_BATT4: C65.1, C78.1, D30.A, J34.12, J39.2, R58.2, U13.2, U13.3, U16.3
V_BATT5: C81.1, C94.1, D36.A, J42.12, J47.2, R71.2, U17.2, U17.3, U20.3
V_BATT6: C97.1, C110.1, D42.A, J50.12, J55.2, R84.2, U21.2, U21.3, U24.3
V_BATT7: C113.1, C126.1, D48.A, J58.12, J63.2, R97.2, U25.2, U25.3, U29.3
V_BATT8: C129.1, C142.1, D54.A, J66.12, J71.2, R110.2, U30.2, U30.3, U33.3
V_BATT9: C145.1, C158.1, D60.A, J74.12, J79.2, R123.2, U35.2, U35.3, U38.3
V_USB: BYP1.1, C3.1, F1.1, J1.9, J3.10, J5.VBUS1, J5.VBUS2
V_USB1: BYP2.1, C22.1, F2.1, J10.10, J13.9, J14.VBUS1, J14.VBUS2
V_USB2: BYP3.1, C38.1, F3.1, J18.10, J21.9, J22.VBUS1, J22.VBUS2
V_USB3: BYP4.1, C54.1, F4.1, J26.10, J29.9, J30.VBUS1, J30.VBUS2
V_USB4: BYP5.1, C70.1, F5.1, J34.10, J37.9, J38.VBUS1, J38.VBUS2
V_USB5: BYP6.1, C86.1, F6.1, J42.10, J45.9, J46.VBUS1, J46.VBUS2
V_USB6: BYP7.1, C102.1, F7.1, J50.10, J53.9, J54.VBUS1, J54.VBUS2
V_USB7: BYP8.1, C118.1, F8.1, J58.10, J61.9, J62.VBUS1, J62.VBUS2
V_USB8: BYP9.1, C134.1, F9.1, J66.10, J69.9, J70.VBUS1, J70.VBUS2
V_USB9: BYP10.1, C150.1, F10.1, J74.10, J77.9, J78.VBUS1, J78.VBUS2

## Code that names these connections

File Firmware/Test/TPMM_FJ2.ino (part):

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#define COPI 51
#define SCK 52
#define CS 53
#define MICROMOD_D1 2
#define MICROMOD_G3 3
#define MICROMOD_G4 5
#define MICROMOD_G5 6
#define MICROMOD_SCK 7
#define MICROMOD_COPI 8
#define MICROMOD_G6 14
#define MICROMOD_CIPO 15
#define MICROMOD_nBOOT 17
#define MICROMOD_3V3 A1
#define MICROMOD_QWIIC_PWR A2
#define MICROMOD_nRST A3
#define MICROMOD_EN A4
#define MICROMOD_A0 A5
#define MICROMOD_A1 A6
#define MICROMOD_PWM0 A7
#define MICROMOD_G0 A8
#define MICROMOD_PWM1 A9
#define MICROMOD_G1 A10
#define MICROMOD_D0 A11
#define MICROMOD_G2 A12
#define MICROMOD_SDA 20
#define MICROMOD_SCL 21
#define MICROMOD_QWIIC_PWR_EN 67

// Global macros definitions
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// Sets all FJ2 pins which interface with TPMM to HighZ
void SetPinsHighZ()
{
  pinMode(MICROMOD_D1, INPUT);
  pinMode(MICROMOD_G3, INPUT);
  pinMode(MICROMOD_G4, INPUT);
  pinMode(MICROMOD_G5, INPUT);
  pinMode(MICROMOD_SCK, INPUT);
  pinMode(MICROMOD_COPI, INPUT);
  pinMode(MICROMOD_G6, INPUT);
  pinMode(MICROMOD_CIPO, INPUT);
  pinMode(MICROMOD_A0, INPUT);
  pinMode(MICROMOD_A1, INPUT);
  pinMode(MICROMOD_PWM0, INPUT);
  pinMode(MICROMOD_G0, INPUT);
  pinMode(MICROMOD_PWM1, INPUT);
  pinMode(MICROMOD_G1, INPUT);
  pinMode(MICROMOD_D0, INPUT);
  pinMode(MICROMOD_G2, INPUT);
}

// Sends command to TPMM to set all pins as input pullup. Returns true if TPMM acknowledges the message correctly.
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    return false;
  }
  // Set G0 as output and set it to HIGH
  pinMode(MICROMOD_G0, OUTPUT);
  digitalWrite(MICROMOD_G0, HIGH);
  result = CheckCrosstalk(MICROMOD_G0, HIGH);
  if (!result)
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  }

  // Set G0 as output and set it to LOW
  pinMode(MICROMOD_G0, OUTPUT);
  digitalWrite(MICROMOD_G0, LOW);
  result = CheckCrosstalk(MICROMOD_G0, LOW);
  if (!result)
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    return false;
  }
  // Set G1 as output and set it to HIGH
  pinMode(MICROMOD_G1, OUTPUT);
  digitalWrite(MICROMOD_G1, HIGH);
  result = CheckCrosstalk(MICROMOD_G1, HIGH);
  if (!result)
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  }

  // Set G1 as output and set it to LOW
  pinMode(MICROMOD_G1, OUTPUT);
  digitalWrite(MICROMOD_G1, LOW);
  result = CheckCrosstalk(MICROMOD_G1, LOW);
  if (!result)
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    return false;
  }
  // Set G2 as output and set it to HIGH
  pinMode(MICROMOD_G2, OUTPUT);
  digitalWrite(MICROMOD_G2, HIGH);
  result = CheckCrosstalk(MICROMOD_G2, HIGH);
  if (!result)
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  }

  // Set G2 as output and set it to LOW
  pinMode(MICROMOD_G2, OUTPUT);
  digitalWrite(MICROMOD_G2, LOW);
  result = CheckCrosstalk(MICROMOD_G2, LOW);
  if (!result)
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    return false;
  }
  // Set G5 as output and set it to HIGH
  pinMode(MICROMOD_G5, OUTPUT);
  digitalWrite(MICROMOD_G5, HIGH);
  result = CheckCrosstalk(MICROMOD_G5, HIGH);
  if (!result)
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  }

  // Set G5 as output and set it to LOW
  pinMode(MICROMOD_G5, OUTPUT);
  digitalWrite(MICROMOD_G5, LOW);
  result = CheckCrosstalk(MICROMOD_G5, LOW);
  if (!result)
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    return false;
  }
  // Set G6 as output and set it to HIGH
  pinMode(MICROMOD_G6, OUTPUT);
  digitalWrite(MICROMOD_G6, HIGH);
  result = CheckCrosstalk(MICROMOD_G6, HIGH);
  if (!result)
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  }

  // Set G6 as output and set it to LOW
  pinMode(MICROMOD_G6, OUTPUT);
  digitalWrite(MICROMOD_G6, LOW);
  result = CheckCrosstalk(MICROMOD_G6, LOW);
  if (!result)
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    return false;
  }
  // Set CIPO as output and set it to HIGH
  pinMode(MICROMOD_CIPO, OUTPUT);
  digitalWrite(MICROMOD_CIPO, HIGH);
  result = CheckCrosstalk(MICROMOD_CIPO, HIGH);
  if (!result)
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  }

  // Set CIPO as output and set it to LOW
  pinMode(MICROMOD_CIPO, OUTPUT);
  digitalWrite(MICROMOD_CIPO, LOW);
  result = CheckCrosstalk(MICROMOD_CIPO, LOW);
  if (!result)
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    return false;
  }
  // Set COPI as output and set it to HIGH
  pinMode(MICROMOD_COPI, OUTPUT);
  digitalWrite(MICROMOD_COPI, HIGH);
  result = CheckCrosstalk(MICROMOD_COPI, HIGH);
  if (!result)
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  }

  // Set COPI as output and set it to LOW
  pinMode(MICROMOD_COPI, OUTPUT);
  digitalWrite(MICROMOD_COPI, LOW);
  result = CheckCrosstalk(MICROMOD_COPI, LOW);
  if (!result)
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    return false;
  }
  // Set SCK as output and set it to HIGH
  pinMode(MICROMOD_SCK, OUTPUT);
  digitalWrite(MICROMOD_SCK, HIGH);
  result = CheckCrosstalk(MICROMOD_SCK, HIGH);
  if (!result)
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  }

  // Set SCK as output and set it to LOW
  pinMode(MICROMOD_SCK, OUTPUT);
  digitalWrite(MICROMOD_SCK, LOW);
  result = CheckCrosstalk(MICROMOD_SCK, LOW);
  if (!result)
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    return false;
  }
  // Set D1 as output and set it to HIGH
  pinMode(MICROMOD_D1, OUTPUT);
  digitalWrite(MICROMOD_D1, HIGH);
  result = CheckCrosstalk(MICROMOD_D1, HIGH);
  if (!result)
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  }

  // Set D1 as output and set it to LOW
  pinMode(MICROMOD_D1, OUTPUT);
  digitalWrite(MICROMOD_D1, LOW);
  result = CheckCrosstalk(MICROMOD_D1, LOW);
  if (!result)
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    return false;
  }
  // Set D0 as output and set it to HIGH
  pinMode(MICROMOD_D0, OUTPUT);
  digitalWrite(MICROMOD_D0, HIGH);
  result = CheckCrosstalk(MICROMOD_D0, HIGH);
  if (!result)
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  }

  // Set D0 as output and set it to LOW
  pinMode(MICROMOD_D0, OUTPUT);
  digitalWrite(MICROMOD_D0, LOW);
  result = CheckCrosstalk(MICROMOD_D0, LOW);
  if (!result)
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    return false;
  }
  // Set PWM1 as output and set it to HIGH
  pinMode(MICROMOD_PWM1, OUTPUT);
  digitalWrite(MICROMOD_PWM1, HIGH);
  result = CheckCrosstalk(MICROMOD_PWM1, HIGH);
  if (!result)
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  }

  // Set PWM1 as output and set it to LOW
  pinMode(MICROMOD_PWM1, OUTPUT);
  digitalWrite(MICROMOD_PWM1, LOW);
  result = CheckCrosstalk(MICROMOD_PWM1, LOW);
  if (!result)
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    return false;
  }
  // Set PWM0 as output and set it to HIGH
  pinMode(MICROMOD_PWM0, OUTPUT);
  digitalWrite(MICROMOD_PWM0, HIGH);
  result = CheckCrosstalk(MICROMOD_PWM0, HIGH);
  if (!result)
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  }

  // Set PWM0 as output and set it to LOW
  pinMode(MICROMOD_PWM0, OUTPUT);
  digitalWrite(MICROMOD_PWM0, LOW);
  result = CheckCrosstalk(MICROMOD_PWM0, LOW);
  if (!result)
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bool AnalogPinsCheck()
{
  SetPinsHighZ();
  pinMode(MICROMOD_A0, OUTPUT);
  pinMode(MICROMOD_A1, OUTPUT);
  digitalWrite(MICROMOD_A0, LOW);
  digitalWrite(MICROMOD_A1, LOW);
  Serial.print(F("Step 10.1: Checking analog reading when driven to ground..."));
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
